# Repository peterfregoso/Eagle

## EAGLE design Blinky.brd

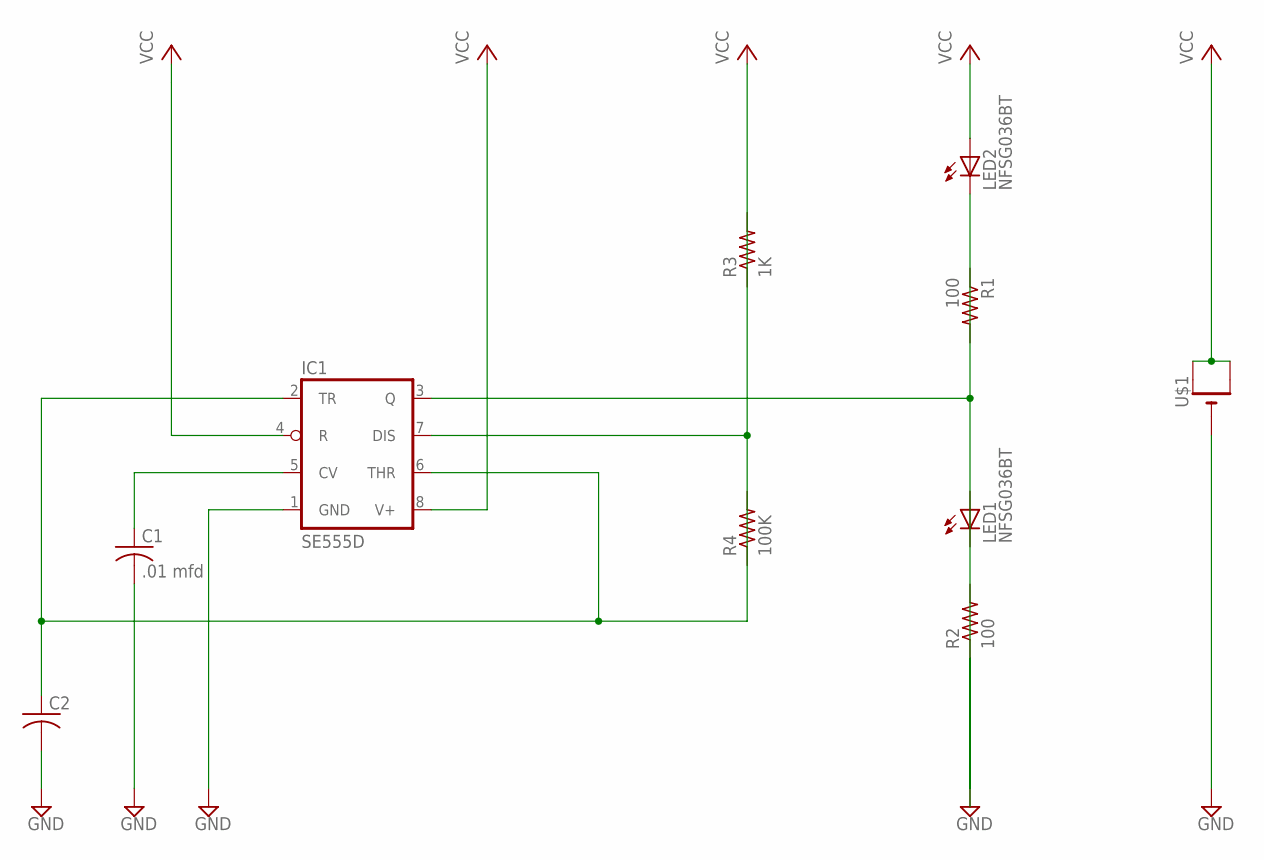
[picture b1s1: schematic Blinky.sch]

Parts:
C1: .01 mfd; C0805
C2: C-USC0805; C0805
IC1: SE555D; SO08
LED1, LED2: NFSG036BT
R1, R2: 100; M0805
R3: 1K; M0805
R4: 100K; M0805
U$1: CR1220THM; CR1220-THM

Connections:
GND: C1.2, C2.2, IC1.1 (GND), IC1.3 (Q), LED2.C, R2.1, U$1.-
unnamed: C1.1, IC1.5 (CV)
VCC: C2.1, IC1.2 (TR), IC1.4 (R), IC1.6 (THR), IC1.7 (DIS), IC1.8 (V+), LED2.A, U$1.+1 (+), U$1.+2 (+1)

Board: 2 copper layers, 10 parts (0 on the bottom side), 3 nets, no tracks yet.

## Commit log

2018-02-24 blinky
    Fun
